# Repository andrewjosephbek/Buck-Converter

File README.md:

PCB and BOM for 5V Buck Converter, SK internal use. See [Buck Converter Tester](https://github.com/andrewjosephbek/Buck-Converter-Tester).

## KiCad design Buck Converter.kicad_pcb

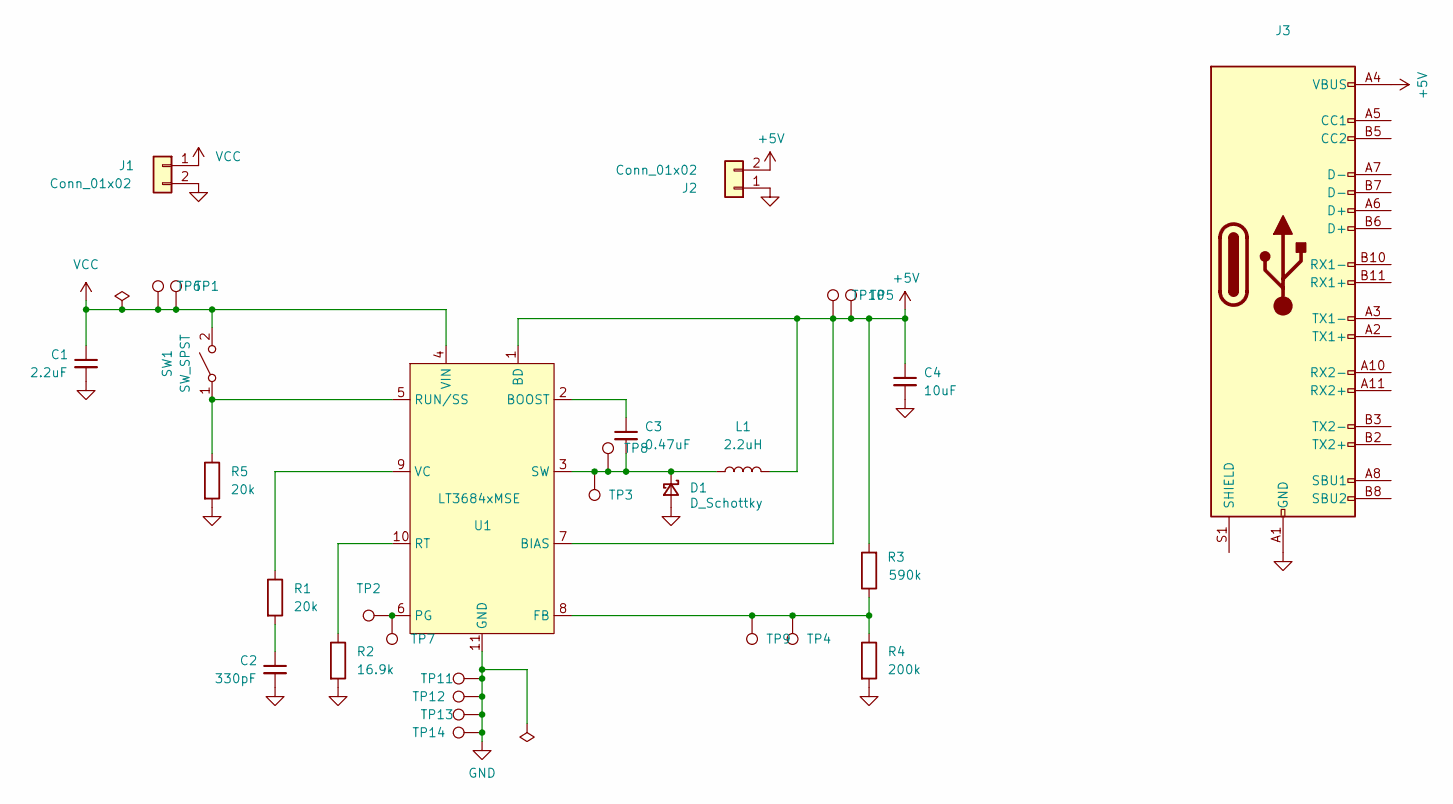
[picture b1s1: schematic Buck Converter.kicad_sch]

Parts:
C1: 2.2uF; C_0603_1608Metric_Pad1.08x0.95mm_HandSolder
C2: 330pF; C_0603_1608Metric_Pad1.08x0.95mm_HandSolder
C3: 0.47uF; C_0603_1608Metric_Pad1.08x0.95mm_HandSolder
C4: 10uF; C_1206_3216Metric_Pad1.33x1.80mm_HandSolder
D1: D_Schottky; D_SMA_Handsoldering
J1, J2: Conn_01x02; PhoenixContact_MSTBVA_2,5_2-G_1x02_P5.00mm_Vertical
J3: (no value)
L1: 2.2uH; L_Vishay_IHLP-2020
R1, R5: 20k; R_0603_1608Metric_Pad0.98x0.95mm_HandSolder
R2: 16.9k; R_0603_1608Metric_Pad0.98x0.95mm_HandSolder
R3: 590k; R_0603_1608Metric_Pad0.98x0.95mm_HandSolder
R4: 200k; R_0603_1608Metric_Pad0.98x0.95mm_HandSolder
SW1: SW_SPST; SW_SPDT_CK-JS102011SAQN
TP1, TP2, TP3, TP4, TP5, TP13, TP14: TestPoint; TestPoint_Keystone_5000-5004_Miniature
TP6, TP7, TP8, TP9, TP10, TP11, TP12: TestPoint; TestPoint_Pad_2.0x2.0mm
U1: LT3684xMSE; MSOP-10-1EP_3x3mm_P0.5mm_EP1.68x1.88mm

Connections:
+5V: C4.1, J2.2, J3.A4 (VBUS), J3.A9 (VBUS), J3.B4 (VBUS), J3.B9 (VBUS), L1.2, R3.2, TP5.1, TP10.1, U1.1 (BD), U1.7 (BIAS)
GND: C1.2, C2.2, C4.2, D1.2 (A), J1.2, J2.1, J3.A1 (GND), J3.A12 (GND), J3.B1 (GND), J3.B12 (GND), R2.2, R4.2, R5.2, TP11.1, TP12.1, TP13.1, TP14.1, U1.11 (GND)
unnamed: C2.1, R1.2
unnamed: C3.1, U1.2 (BOOST)
unnamed: C3.2, D1.1 (K), L1.1, TP3.1, TP8.1, U1.3 (SW)
unnamed: R1.1, U1.9 (VC)
unnamed: R2.1, U1.10 (RT)
unnamed: R3.1, R4.1, TP4.1, TP9.1, U1.8 (FB)
unnamed: R5.1, SW1.1 (A), U1.5 (RUN/SS)
unnamed: TP2.1, TP7.1, U1.6 (PG)
VCC: C1.1, J1.1, SW1.2 (B), TP1.1, TP6.1, U1.4 (VIN)

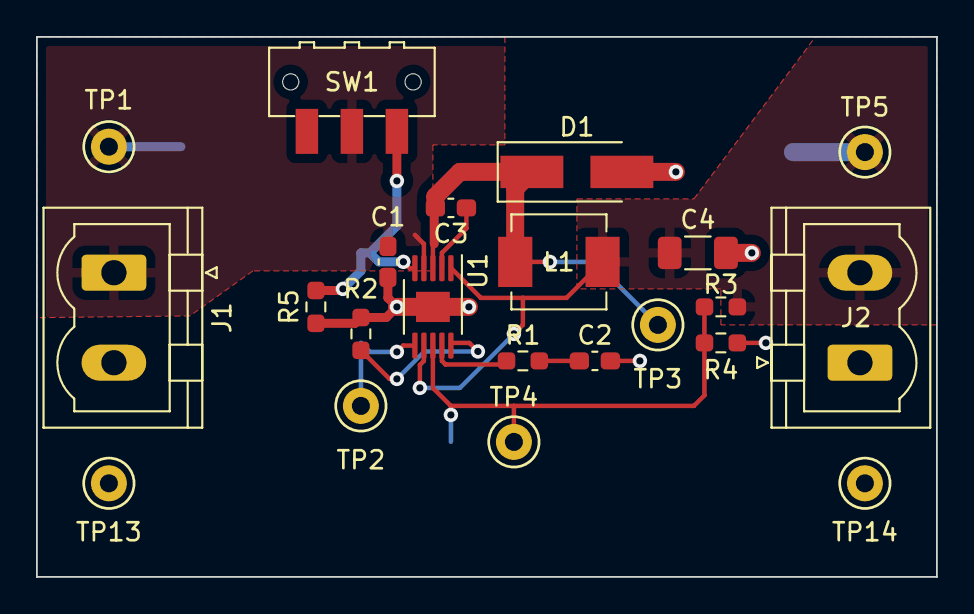
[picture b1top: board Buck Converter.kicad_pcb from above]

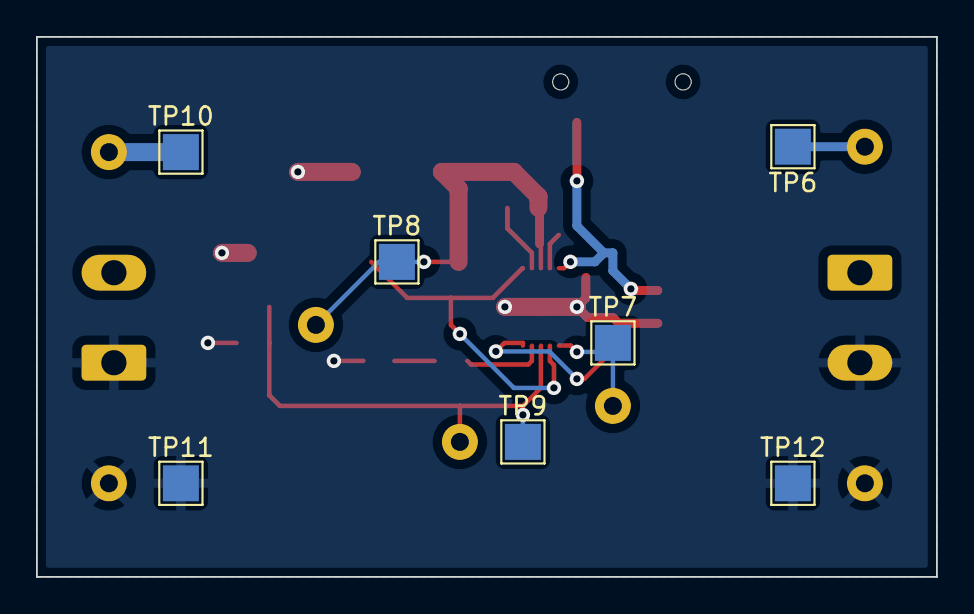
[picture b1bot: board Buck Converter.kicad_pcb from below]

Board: 2 copper layers, 50.0 x 30.0 mm, 29 parts (7 on the bottom side), 11 nets.

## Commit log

2022-06-19 Minor Tweaks
    Updated PCB with the following recommendations:
    1. Clean up the ERC and DRC issues. The schematic has the USB connector without it being on the PCB; there's an unmade connection on TP6, and the silkscreen needs to be cleaned up.
    2. Move the switch inward from the edge of the board. The holes are close enough to the edge to cause some grief.
    3. Move R5 a bit south. It's an easy fix to clear up the path for VCC to get from J1.1 to U1.4. Also to make way for:
    3. Move C1 closer to the IC. The bypass caps should be as close as possible to their associated ICs.
2022-06-22 Made layout changes as per Seth's reccomendations
    1. Clean up the ERC and DRC issues. The schematic has the USB connector without it being on the PCB; there's an unmade connection on TP6, and the silkscreen needs to be cleaned up.
    2. Move the switch inward from the edge of the board. The holes are close enough to the edge to cause some grief.
    3. Move R5 a bit south. It's an easy fix to clear up the path for VCC to get from J1.1 to U1.4. Also to make way for:
    3. Move C1 closer to the IC. The bypass caps should be as close as possible to their associated ICs.
    4. The connection between U1.3 and C3.2 is a bit thin. That's part of the power path, however, I also recognize that it's a prett
2022-06-27 5V, VCC, GND and Version silkscreen
    Added front silkscreen text in top left corner of board for version number. Labeled 5V, VCC, and GND terminals in back silkscreen text.
2022-07-05 Silkscreen Updates
    Added version numbers and made silkscreen readable
2026-01-12 Organized files
2026-02-18 images
